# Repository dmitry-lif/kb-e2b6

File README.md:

# KB-E2B6: your own illuminated controls, as a USB keyboard

> [!NOTE]
> **This project is still a work in progress.** Some materials are missing (photos, measurements, a few sections of the docs). Everything still open is marked:
>
> -  a missing piece, with a note in italics on what will go there;
> - the **WORK IN PROGRESS** bar at the top of a page: that page still has open items.

KB-E2B6 is a small (45 × 35 mm) open-source controller for physical controls. You connect up to two rotary encoders with push switches and six push buttons, all of them backlit if you like, and run one USB cable to the host. The host sees an ordinary USB keyboard. You choose once, in a web page (the configurator), what each control sends, and the controller remembers this setup.

You can bring your own encoders and buttons, or start from the **[REFERENCE KIT](docs/kit.md)**: the controller with the encoders, buttons, adapter boards and cables I use myself, tested together, so you have everything you need to hook it up.

I built it for the Android head unit in my car, but nothing about it is car-specific. It should work with anything that accepts a USB keyboard: a PC or media centre, a phone or tablet, a Raspberry Pi, a robot, a simulator panel, or any project that needs a few good physical controls.

> Just want to use it? → **[GETTING STARTED](docs/getting-started.md)**.

**How it fits together.** Up to two backlit rotary encoders and six backlit push buttons plug into the 45 × 35 mm controller. One USB cable goes to the host (a car head unit, PC, phone or robot), which sees an ordinary keyboard. You set it up once from a computer with the configurator; on Android, the optional Key Mapper app turns the keys into app actions, such as F1 → open the maps app.

## Why I built it

When the infotainment system of my 2020 KIA Sorento died, I replaced it with a 10" Android head unit: big screen, modern UI, and not a single physical button. Head units with buttons exist, but they usually have only one or a few, the buttons take space away from the screen, and the units cost more. What I really wanted were controls that look like they came with the car: built into the dashboard, backlit like the originals, sized to fit the tight frame around the new unit, and doing exactly what I want.

Android already understands a USB keyboard, so the controls didn't need a custom app or driver. What was missing was a small controller that reads encoders and buttons, drives their backlight, runs from the head unit's USB port and is easy to set up. For the actions a plain key press can't reach, I use the open-source **[KEY MAPPER](https://github.com/keymapperorg/KeyMapper)** app on the head unit.

Key Mapper turned out to matter for a second reason. Once the controller is installed behind the dashboard, getting it back out to plug into a laptop is a real job, however easy the configurator is. So some of my buttons send plain F-keys, and Key Mapper on the head unit decides what they do. When I change my mind about a button, I remap it on the screen in a minute, without touching the dash. → [The full story](docs/story.md)

**The head unit with the KB-E2B6 behind the dashboard.** Day and night, real photos.

## At a glance

- **Inputs:** 2 rotary encoders with push switch and 6 push buttons. Use as many as you need; unused ports do nothing.
- **Backlight:** every control can be lit, softly enough for night driving. All the LEDs share one supply that the controller dims together. The button on the board turns them on or off and steps the brightness, and the level is remembered. Your own controls do this only if you give them backlight actions (I use long presses).
- **Adapter boards:** small boards that connect the reference kit's encoders and buttons (or your own) to the controller with ready-made cables (an encoder sits on its adapter; a button's adapter sits in its cable). Their solder jumpers (pairs of pads you join with solder) set each control's LED current up or down, so different LEDs can be matched in brightness and none gets brighter than you set.
- **Gestures:** short press, long press and repeat-while-held on every push button and encoder push switch; one action per detent in each direction on encoders with as many pulses as detents.
- **Actions:** keyboard and media keys from a curated list: volume, mute, play/pause, next/previous, Home, Back, Menu, screen brightness, arrows, Enter, Esc, F1–F24, letters and digits, with Ctrl/Shift/Alt/Win combinations, plus backlight actions (on/off, brighter, dimmer).
- **Configuration:** a plain web page you open from disk in Google Chrome, Microsoft Edge, Brave or Opera (other Chromium-based browsers should work too) on a Linux (with a udev rule), Windows or Mac computer (Windows and Mac not tested yet). Pick actions from dropdowns, click **Save to device**. No app, driver, account or internet connection.
- **Power:** from the USB port it plugs into: 17 mA for the board alone, about 30 mA with the 8 controls of my [control box](#the-hardware) lit for daylight.

## Car-minded details

The car shaped a few decisions:

- ESD protection diodes on all 12 input lines and on the USB data lines.
- The LED rail goes through a current-limited switch, an "eFuse" (TPS2553, about 135 mA). A shorted LED cable should be current-limited instead of dragging down the USB supply.
- Flash holds two setup slots: the current setup and the previous one. A save goes to the spare slot, which is read back and checked before the board switches to it, so a power cut in the middle of a save should leave the previous setup in place.
- There's no built-in fallback mapping. If the newest saved setup is damaged, the board should fall back to the previous one you saved, if there is one; **if there's no usable setup at all, the controls stay silent**.
- It runs from 5 V USB only. It is **not** for direct connection to a car's 12 V, and it is not certified automotive equipment.

## Get going in 3 steps

1. **Connect the controls.** Encoders go to `ENC 1` / `ENC 2`, buttons to `BTN 1` … `BTN 6` (names on the back of the board; the top shows E1, E2, B1–B6). The reference encoders and buttons sit on small adapter boards with ready-made cables, and the plugs only fit one way: plug each cable so its red wire is on `LED+` at both ends ([why](docs/wiring.md#cables-to-the-adapter-boards)). You can also wire up your own controls. **Using an RGB encoder? Solder its colour jumper first** (see [the hardware](#the-hardware)).
2. **Configure it once, on a computer.** Download the project ([on GitHub](https://github.com/dmitry-lif/kb-e2b6): green *Code* button → *Download ZIP*), unzip it, open `web_config/index.html` in Chrome, Edge, Brave or Opera, plug the board in, click **Connect device**, choose what each control does and click **Save to device**. **A new board does nothing until you've done this.** Use a USB cable that carries data. (Firefox, Safari and phone or head-unit browsers can't do this step.) **On Linux, once, before you connect**, run this in a terminal from the unzipped folder:

   ```bash
   web_config/linux/install-udev-rule.sh
   ```

   Still can't connect on Linux: [this check](docs/troubleshooting.md#linux-still-cant-connect).

3. **Plug it into your head unit, PC or tablet.** The red status LED should show its heartbeat (two short flashes every second) and your controls should work. Fast blinking means there's no saved setup: back to [step 2](#get-going-in-3-steps).

> Step by step, with what you should see at each point: **[GETTING STARTED](docs/getting-started.md)**.

**The configurator.** The web page connected to a board: the toolbar with **Save to device**, the status strip (serial number, firmware version, *Config A* / *Config B*) and cards for the general settings, the encoders and the buttons, each set with dropdowns. The labels match the real page; the layout in this picture is approximate.

## The hardware

The controller works with any encoders and buttons that switch to ground. The adapter boards make the reference parts plug-and-play and set their LED current with solder jumpers. Everything is in [`hardware/`](hardware/): KiCad 9 projects plus Gerber, BOM and pick-and-place files for JLCPCB in each `manufacturing/` folder (Gerbers only for the cover plate).

| Board | What it is | KiCad project |
|---|---|---|
| **KB-E2B6 controller** | 45 × 35 mm, STM32G474, USB-C, 2 × 6-pin encoder ports, 6 × 4-pin button ports, on-board button (LED on/off and brightness), status LED, 4-pin SWD header | [`hardware/kb_e2b6_hw_v2.kicad_pro`](hardware/kb_e2b6_hw_v2.kicad_pro) |
| **Encoder adapter** | Holds an EC12 encoder with a single-colour LED; jumpers set the LED current | [`hardware/encoder_db/`](hardware/encoder_db/) |
| **RGB encoder adapter** | Holds an EC12 RGB encoder; jumpers set the LED current and the colour. **No colour is selected from the factory** (see below) | [`hardware/encoder_rgb_db/`](hardware/encoder_rgb_db/) |
| **Button adapter** | Sits in the cable between the controller and an LED push button; jumpers set the LED current | [`hardware/button_db/`](hardware/button_db/) |
| **Cover plate** | 45 × 35 mm PCB lid for the controller | [`hardware/cover/`](hardware/cover/) |

> [!IMPORTANT]
> **RGB encoder adapter: choose the colour before you install it.** Its three colour jumpers (R, G, B) all come open, so the encoder's LED stays dark until you bridge one of them with a soldering iron. Bridge one only: colours can't be mixed. Which jumper is which: [Hardware notes](docs/hardware.md#rgb-encoder-adapter).

> [!NOTE]
> One detail worth a look is the RGB encoder adapter. The RGB encoders I use as reference parts share one pin between the switch and the LEDs, so the usual dimming (switching the LED's minus side) can't work. A small P-MOSFET on the adapter, driven by the controller's dimmed LED pair, switches the LED supply instead: same cable, same port, no firmware change.

> How the boards work, part by part, with the trade-offs: **[Hardware notes](docs/hardware.md)**. Making your own: **[Building your own](docs/building.md)**.

**The controller, rev 2.1.** KiCad 3D render of the 45 × 35 mm board: the 6-pin encoder ports (E1, E2) and 4-pin button ports (B1–B6) along the two long edges, the STM32 in the middle, the USB-C socket on the left edge, and the status LED, the on-board button and the SWD connection (3V3, SWIO, SWCLK, GND) on the right.

**The real controller, all eight ports cabled.** Left: with the cover plate screwed on. Right: the back, where the silkscreen names every port (`ENC 1`, `ENC 2`, `BTN 1` … `BTN 6`) and its pins.

**The controller with its controls.** Two encoders sit on their adapter boards; each of the six push buttons connects through a button adapter in its cable. Every control has one cable to its port.

**A control box built around the controller.** Left: the front panel, with two backlit encoders and six backlit buttons in different colours, at a brightness clearly visible in daylight: the whole box draws about 30 mA ([Specs](#specs)). Right: the box opened, with the controller at the bottom, the encoders and buttons with their adapter boards in the lid, and the cables between them. One example of what you can build; the box and these controls are not part of the [reference kit](docs/kit.md).

## Firmware and configurator

The firmware is Rust on [Embassy](https://embassy.dev): `no_std`, no heap, and an input scan loop that never waits on anything. Its settings are a fixed-size, CRC-checked binary validated by the same Rust code in the firmware and in the `crs-pack` command-line tool. A setup only takes effect at boot, so **Save to device** writes the spare setup slot and restarts the board (a couple of seconds). That keeps a single, well-trodden startup path instead of a second "apply live" path.

The configurator is plain HTML and JavaScript with no build step. It talks to the board over WebHID (the USB access built into Chromium-based browsers) through a separate vendor-defined HID interface, next to the keyboard.

- Build, flash, recovery: [`firmware/README.md`](firmware/README.md)
- How the firmware is organised, and why: [`firmware/docs/ARCHITECTURE.md`](firmware/docs/ARCHITECTURE.md)
- Using the configurator, with screenshots and example setups: [`docs/configuring.md`](docs/configuring.md); its files: [`web_config/README.md`](web_config/README.md)

## Status

This is the first public snapshot: controller rev 2.1, adapter boards rev 2.0, firmware 2.1.0.

## Specs

| | |
|---|---|
| Inputs | 2 rotary encoders (with push switch), 6 push buttons, 1 on-board button (LED on/off and brightness) |
| Output to host | USB HID keyboard + consumer (media) keys; also a serial debug console (CDC) and a WebHID configuration interface |
| Host connector | USB-C (USB 2.0 full speed) |
| Control connectors | JST GH-compatible 1.25 mm: 2 × 6-pin (encoders), 6 × 4-pin (buttons) |
| Programming | 4-pin 2.54 mm SWD header (no reset pin) |
| Power | 5 V from USB only. **Not** for direct connection to a car's 12 V |
| LEDs | One shared 5 V rail, current-limited (TPS2553, ~135 mA nominal), PWM-dimmed together at 1 kHz |
| Consumption | 17 mA for the board alone. With 8 controls lit (2 encoders, 6 buttons): about 19 mA at the lowest brightness, about 30 mA at a brightness clearly visible in daylight, as in the [control box photo](#the-hardware). Measured on that box; other LEDs not tested |
| MCU | STM32G474CBT6, 170 MHz, 128 KiB flash, no crystal |
| Size | 45 × 35 mm, 4 × M2 mounting holes |
| Configure with | Google Chrome, Microsoft Edge, Brave or Opera (Chromium-based browsers) on a Linux (needs a udev rule), Windows or Mac computer (Windows and Mac not tested yet); the page runs locally |

## FAQ

**Does it work with my head unit?** If it accepts a USB keyboard, it should. Easy test before you buy: plug any USB keyboard with media keys into the head unit's USB port. If the volume and arrow keys work, the controller should work too. In my own car: a **10" Mekede DUDU 4 running Android 10**. Mapping some Android system actions with Key Mapper has limits: I was surprised to find that many trivial ones need extra permissions (easy to grant by following Key Mapper's in-app guides), and some even need further Android tweaks over the debug interface. I didn't go that far: for my use case the standard keys were enough.

**Does the backlight follow my car's dash dimmer?** No, the controller has no input for it. You set the level yourself and it stays there. You can also give your controls backlight actions (I put them on long presses, as a secondary function).

**Can I configure it on the head unit itself?** No. Browsers on Android (and Firefox and Safari anywhere) can't talk to USB devices this way. Use a computer once; the setup stays in the controller.

**Can I change what a button does after it's installed?** Yes: reconnect it to a computer and save a new setup, or give the controls arbitrary keys (say F-keys) once and remap them on the host, on Android with [Key Mapper](https://github.com/keymapperorg/KeyMapper), on a PC with any key-remapping tool. Backlight actions can only be assigned in the configurator. Details: [Getting started](docs/getting-started.md#4-plug-it-into-your-host).

**What if I mess up the setup?** By design, the board checks every setup before saving it, refuses an invalid one and keeps the old setup. Just fix it in the configurator and click **Save to device** again.

**Can I use my own encoders and buttons?** Yes. Encoders: any EC11/EC12-style one with as many pulses as detents. Buttons: any momentary type. Both must switch to ground. LEDs need their own series resistor (the adapter boards have them). What I learned picking mine: [choosing controls](docs/choosing-controls.md).

**Can I update the firmware over USB?** Not in 2.1.0. Firmware updates need an SWD probe; the configurator only changes the setup.

## Get one, build one, or get in touch

- **The reference kit:** the controller with tested encoders, buttons, adapter boards and cables. What's in it, what you supply and what you still do yourself: **[THE REFERENCE KIT](docs/kit.md)**.
- **Build your own:** order the boards from the files in `hardware/manufacturing/` and `hardware/*/manufacturing/` and flash the MCU ([Building your own](docs/building.md)), then prepare the controls ([Preparing and wiring the controls](docs/wiring.md)) and configure it ([Getting started](docs/getting-started.md)).
- **Feedback, bugs, ideas:** [open an issue](https://github.com/dmitry-lif/kb-e2b6/issues). It's a one-person hobby project, so replies may take a while, but I'd like to hear how you use it.

## Documentation

| | |
|---|---|
| [The reference kit](docs/kit.md) | What's in the kit, what you supply, what you still do |
| [Getting started](docs/getting-started.md) | Connecting the controls, configuring, the backlight, plugging into the host |
| [Troubleshooting, limitations and safety](docs/troubleshooting.md) | Symptoms, configurator messages, known limits, test status, safety |
| [Hardware notes](docs/hardware.md) | How the controller and the adapter boards work, and why |
| [Building your own](docs/building.md) | Ordering the boards, the SWD header, flashing the firmware, first checks |
| [Preparing and wiring the controls](docs/wiring.md) | Ports, wiring rules, soldering the controls onto the adapter boards, cables, bench checks: for the kit's controls and your own |
| [Configuring the controller](docs/configuring.md) | Quick start with screenshots, every option of the configurator, example setups |
| [Firmware](firmware/README.md) | Build, flash, architecture, specs, recovery |
| [The story](docs/story.md) · [Choosing controls](docs/choosing-controls.md) · [Car integration](docs/car-integration.md) | Background, parts I tried, putting it into a car |

## License

© 2026 Dmitry Lifshits. Code (firmware, tools, configurator): [MIT](LICENSE-MIT) or [Apache-2.0](LICENSE-APACHE). Hardware: [CERN-OHL-S-2.0](hardware/LICENSE): if you make and distribute boards based on a modified design, you share the modified design files under the same licence. Docs and images: [CC BY 4.0](docs/LICENSE.md), except a few third-party product images listed there. Third-party crates: [THIRD_PARTY_LICENSES.md](THIRD_PARTY_LICENSES.md).

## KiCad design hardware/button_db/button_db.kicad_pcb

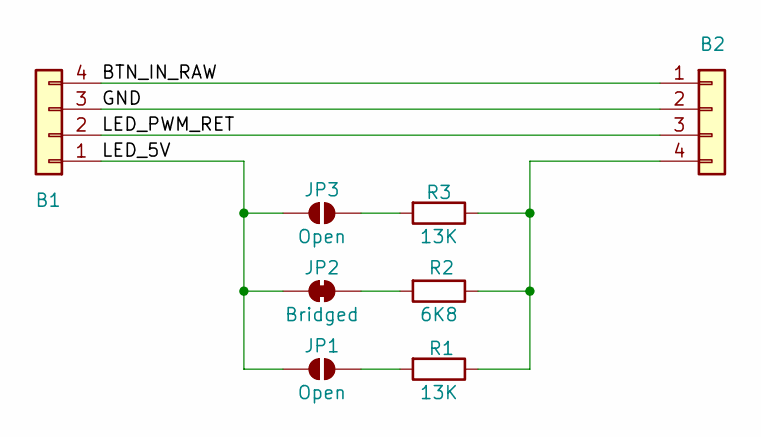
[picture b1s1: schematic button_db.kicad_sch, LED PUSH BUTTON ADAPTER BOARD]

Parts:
B1, B2: Conn_01x04; JST_GH_SM04B-GHS-TB_1x04-1MP_P1.25mm_Horizontal; JLCPCB Part # C51940118
JP1, JP3: Open; SolderJumper-2_P1.3mm_Open_RoundedPad1.0x1.5mm
JP2: Bridged; SolderJumper-2_P1.3mm_Bridged_RoundedPad1.0x1.5mm
R1, R3: 13K; R_0603_1608Metric; JLCPCB Part # C22797
R2: 6K8; R_0603_1608Metric; JLCPCB Part # C23212

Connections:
/BTN_IN_RAW: B1.4, B2.1
/GND: B1.3, B2.2
/LED_5V: B1.1, JP1.2 (B), JP2.2 (B), JP3.2 (B)
/LED_PWM_RET: B1.2, B2.3
unnamed: B2.4, R1.1, R2.1, R3.1
unnamed: JP1.1 (A), R1.2
unnamed: JP2.1 (A), R2.2
unnamed: JP3.1 (A), R3.2

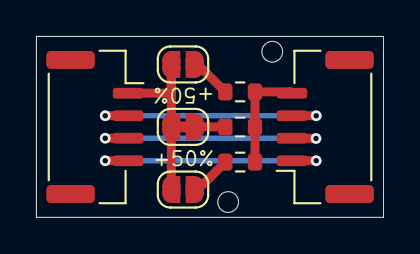
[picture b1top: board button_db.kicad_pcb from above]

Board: 2 copper layers, 19.3 x 10.0 mm, 10 parts (2 on the bottom side), 8 nets.

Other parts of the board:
TH1, TH2: JLCPCB_ToolingHole_1.152mm

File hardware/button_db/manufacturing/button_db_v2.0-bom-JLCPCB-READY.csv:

Comment,Designator,Footprint,JLCPCB Part #
Conn_01x04,"B1,B2",Connector_JST:JST_GH_SM04B-GHS-TB_1x04-1MP_P1.25mm_Horizontal,C51940118
13K,"R1,R3",Resistor_SMD:R_0603_1608Metric,C22797
6K8,R2,Resistor_SMD:R_0603_1608Metric,C23212

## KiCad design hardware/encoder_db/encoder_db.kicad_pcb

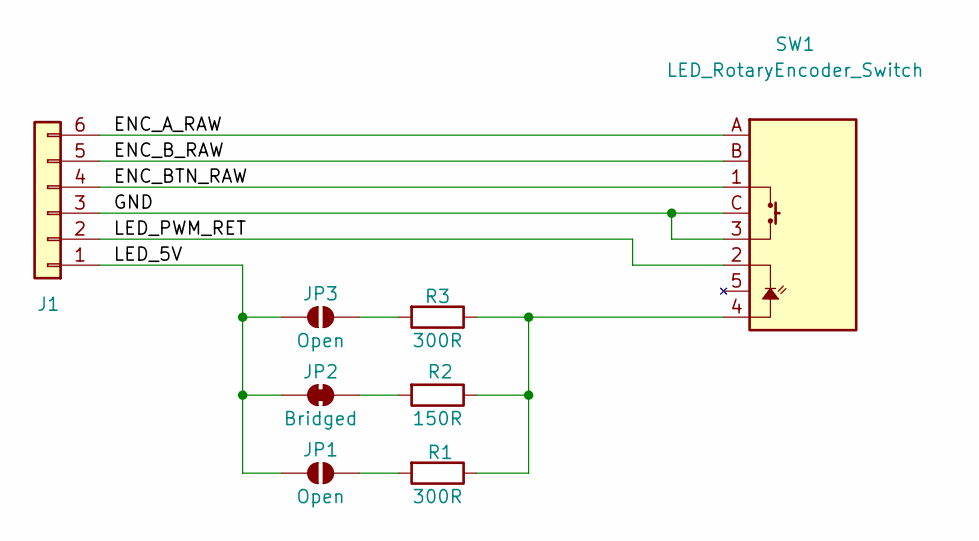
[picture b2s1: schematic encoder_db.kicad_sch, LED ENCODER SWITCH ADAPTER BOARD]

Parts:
J1: Conn_01x06; JST_GH_SM06B-GHS-TB_1x06-1MP_P1.25mm_Horizontal; JLCPCB Part # C51940119
JP1, JP3: Open; SolderJumper-2_P1.3mm_Open_RoundedPad1.0x1.5mm
JP2: Bridged; SolderJumper-2_P1.3mm_Bridged_RoundedPad1.0x1.5mm
R1, R3: 300R; R_0603_1608Metric; JLCPCB Part # C23025
R2: 150R; R_0603_1608Metric; JLCPCB Part # C22808
SW1: LED_RotaryEncoder_Switch; RotaryEncoder_EC12_LED_Switch_Vertical

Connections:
/ENC_A_RAW: J1.6, SW1.A
/ENC_BTN_RAW: J1.4, SW1.1 (SW2)
/ENC_B_RAW: J1.5, SW1.B
/GND: J1.3, SW1.3 (SW1), SW1.C
/LED_5V: J1.1, JP1.2 (B), JP2.2 (B), JP3.2 (B)
/LED_PWM_RET: J1.2, SW1.2 (LED-)
unnamed: JP1.1 (A), R1.2
unnamed: JP2.1 (A), R2.2
unnamed: JP3.1 (A), R3.2
unnamed: R1.1, R2.1, R3.1, SW1.4 (LED+)

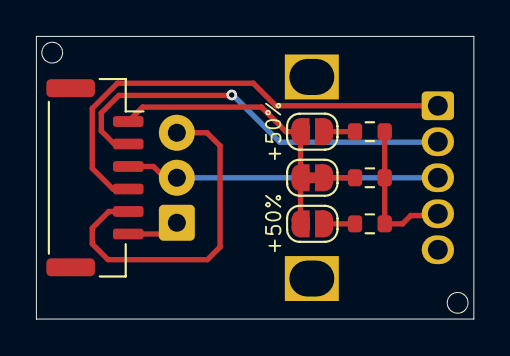
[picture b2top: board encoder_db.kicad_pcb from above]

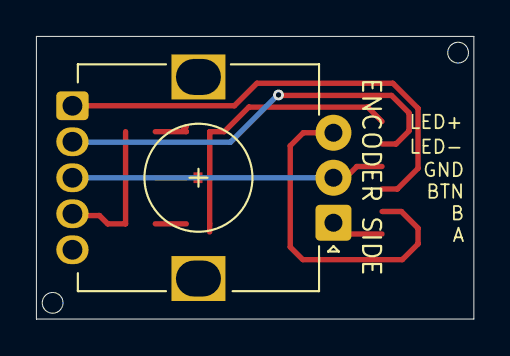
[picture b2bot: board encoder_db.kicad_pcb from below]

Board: 2 copper layers, 24.3 x 15.7 mm, 10 parts (3 on the bottom side), 10 nets.

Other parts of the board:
TH1, TH2: JLCPCB_ToolingHole_1.152mm

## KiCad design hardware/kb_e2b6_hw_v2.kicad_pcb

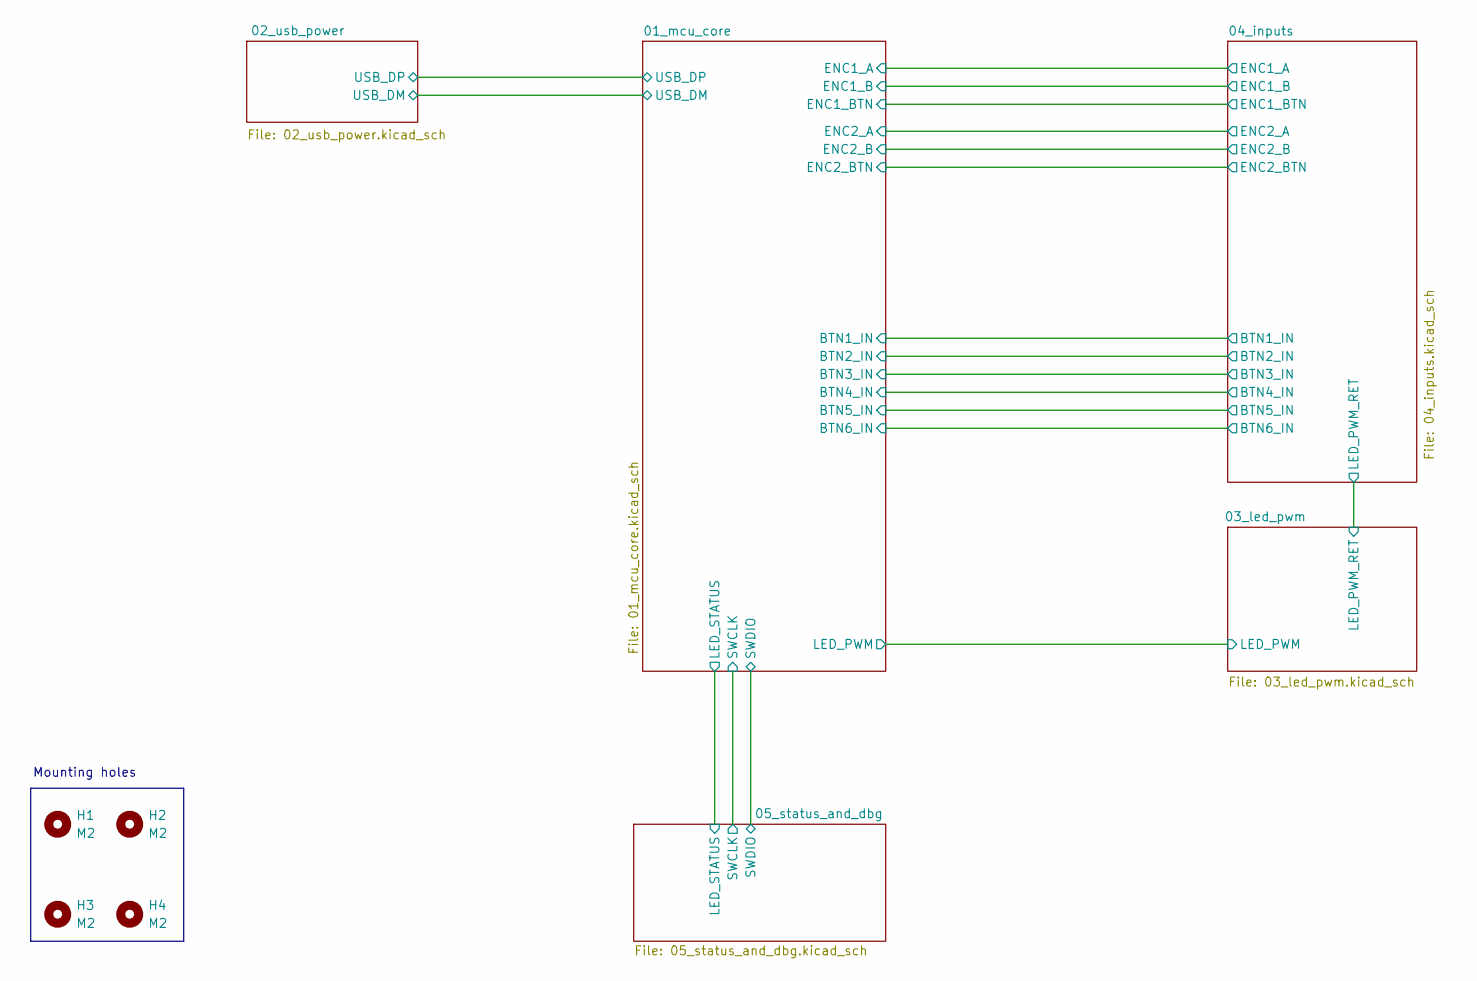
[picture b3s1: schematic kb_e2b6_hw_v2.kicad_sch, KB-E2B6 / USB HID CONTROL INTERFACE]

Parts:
H1, H2, H3, H4: M2; MountingHole_2.2mm_M2

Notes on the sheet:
Mounting holes

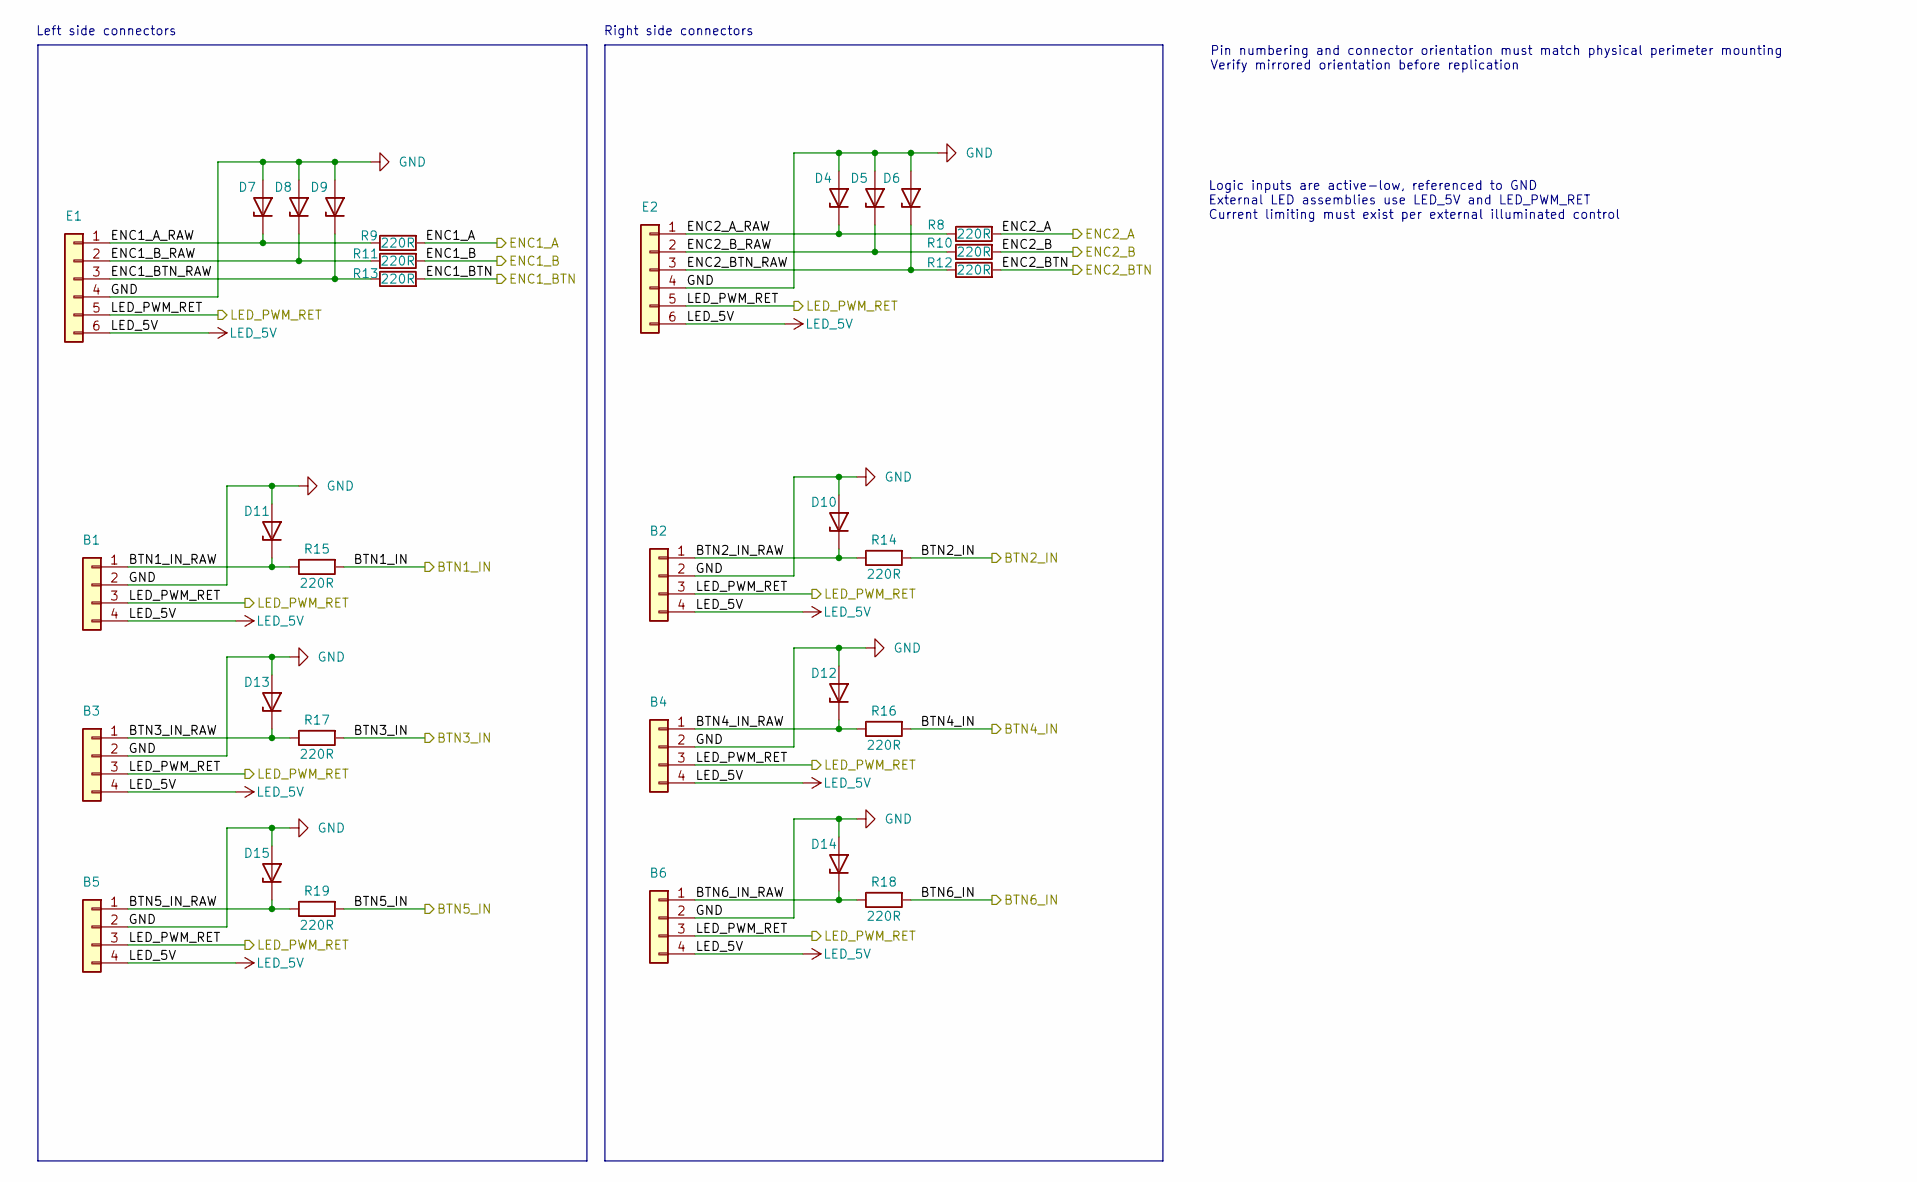
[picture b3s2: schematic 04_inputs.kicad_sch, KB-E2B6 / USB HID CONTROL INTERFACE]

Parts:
B1, B2, B3, B4, B5, B6: Conn_01x04; JST_GH_SM04B-GHS-TB_1x04-1MP_P1.25mm_Horizontal; JLCPCB Part # C51940118
D4, D5, D6, D7, D8, D9, D10, D11, D12, D13, D14, D15: H3V3U10B; D_SOD-882; JLCPCB Part # C20615782
E1, E2: Conn_01x06; JST_GH_SM06B-GHS-TB_1x06-1MP_P1.25mm_Horizontal; JLCPCB Part # C51940119
R8, R9, R10, R11, R12, R13, R14, R15, R16, R17, R18, R19: 220R; R_0402_1005Metric; JLCPCB Part # C25091

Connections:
/01_mcu_core/BTN1_IN: R15.2; also elsewhere on the board
/01_mcu_core/BTN2_IN: R14.2; also elsewhere on the board
/01_mcu_core/BTN3_IN: R17.2; also elsewhere on the board
/01_mcu_core/BTN4_IN: R16.2; also elsewhere on the board
/01_mcu_core/BTN5_IN: R19.2; also elsewhere on the board
/01_mcu_core/BTN6_IN: R18.2; also elsewhere on the board
/01_mcu_core/ENC1_A: R9.2; also elsewhere on the board
/01_mcu_core/ENC1_B: R11.2; also elsewhere on the board
/01_mcu_core/ENC1_BTN: R13.2; also elsewhere on the board
/01_mcu_core/ENC2_A: R8.2; also elsewhere on the board
/01_mcu_core/ENC2_B: R10.2; also elsewhere on the board
/01_mcu_core/ENC2_BTN: R12.2; also elsewhere on the board
/03_led_pwm/LED_PWM_RET: B1.3, B2.3, B3.3, B4.3, B5.3, B6.3, E1.5, E2.5; also elsewhere on the board
/04_inputs/BTN1_IN_RAW: B1.1, D11.1 (K), R15.1
/04_inputs/BTN2_IN_RAW: B2.1, D10.1 (K), R14.1
/04_inputs/BTN3_IN_RAW: B3.1, D13.1 (K), R17.1
/04_inputs/BTN4_IN_RAW: B4.1, D12.1 (K), R16.1
/04_inputs/BTN5_IN_RAW: B5.1, D15.1 (K), R19.1
/04_inputs/BTN6_IN_RAW: B6.1, D14.1 (K), R18.1
/04_inputs/ENC1_A_RAW: D7.1 (K), E1.1, R9.1
/04_inputs/ENC1_BTN_RAW: D9.1 (K), E1.3, R13.1
/04_inputs/ENC1_B_RAW: D8.1 (K), E1.2, R11.1
/04_inputs/ENC2_A_RAW: D4.1 (K), E2.1, R8.1
/04_inputs/ENC2_BTN_RAW: D6.1 (K), E2.3, R12.1
/04_inputs/ENC2_B_RAW: D5.1 (K), E2.2, R10.1
GND: B1.2, B2.2, B3.2, B4.2, B5.2, B6.2, D4.2 (A), D5.2 (A), D6.2 (A), D7.2 (A), D8.2 (A), D9.2 (A), D10.2 (A), D11.2 (A), D12.2 (A), D13.2 (A), D14.2 (A), D15.2 (A), E1.4, E2.4; also elsewhere on the board
LED_5V: B1.4, B2.4, B3.4, B4.4, B5.4, B6.4, E1.6, E2.6; also elsewhere on the board

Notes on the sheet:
Right side connectors
Pin numbering and connector orientation must match physical perimeter mounting Verify mirrored orientation before replication
Left side connectors
Logic inputs are active-low, referenced to GND External LED assemblies use LED_5V and LED_PWM_RET Current limiting must exist per external illuminated control

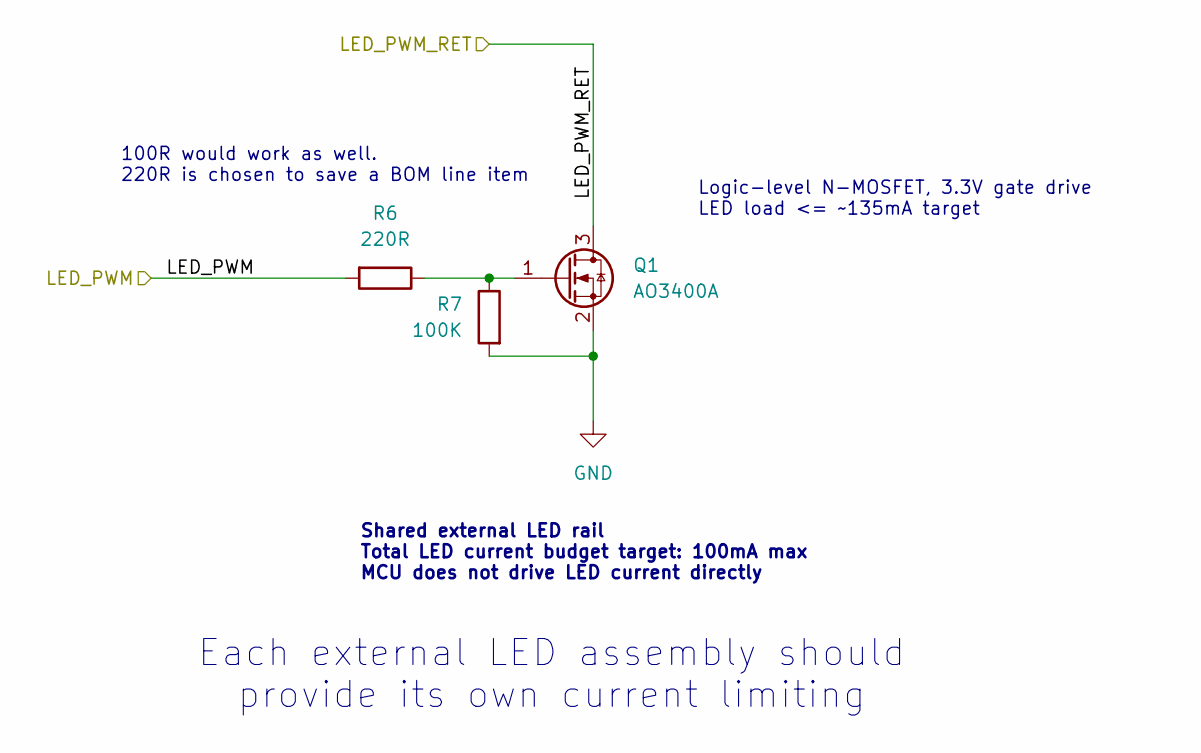
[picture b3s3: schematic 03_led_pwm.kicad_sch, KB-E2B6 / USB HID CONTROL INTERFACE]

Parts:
Q1: AO3400A; SOT-23; JLCPCB Part # C20917
R6: 220R; R_0402_1005Metric; JLCPCB Part # C25091
R7: 100K; R_0402_1005Metric; JLCPCB Part # C25741

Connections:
/01_mcu_core/LED_PWM: R6.2; also elsewhere on the board
/03_led_pwm/LED_PWM_RET: Q1.3 (D); also elsewhere on the board
GND: Q1.2 (S), R7.2; also elsewhere on the board
unnamed: Q1.1 (G), R6.1, R7.1

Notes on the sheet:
Shared external LED rail Total LED current budget target: 100mA max MCU does not drive LED current directly
Logic-level N-MOSFET, 3.3V gate drive LED load <= ~135mA target
100R would work as well. 220R is chosen to save a BOM line item
Each external LED assembly should provide its own current limiting

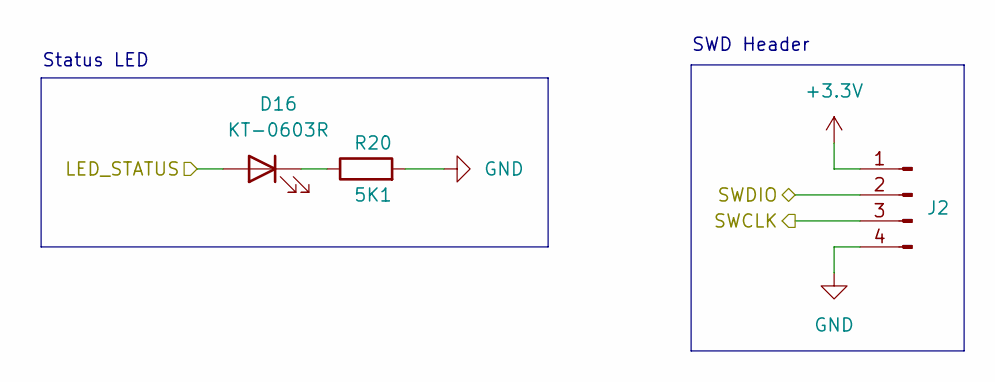
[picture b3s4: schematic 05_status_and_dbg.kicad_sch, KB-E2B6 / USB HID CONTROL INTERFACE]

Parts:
D16: KT-0603R; LED_0603_1608Metric; JLCPCB Part # C2286
J2: Conn_01x04_Pin; PinHeader_1x04_P2.54mm_Vertical
R20: 5K1; R_0402_1005Metric; JLCPCB Part # C25905

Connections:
+3.3V: J2.1; also elsewhere on the board
/01_mcu_core/LED_STATUS: D16.2 (A); also elsewhere on the board
/01_mcu_core/SWCLK: J2.3; also elsewhere on the board
/01_mcu_core/SWDIO: J2.2; also elsewhere on the board
GND: J2.4, R20.2; also elsewhere on the board
unnamed: D16.1 (K), R20.1

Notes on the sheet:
Status LED
SWD Header

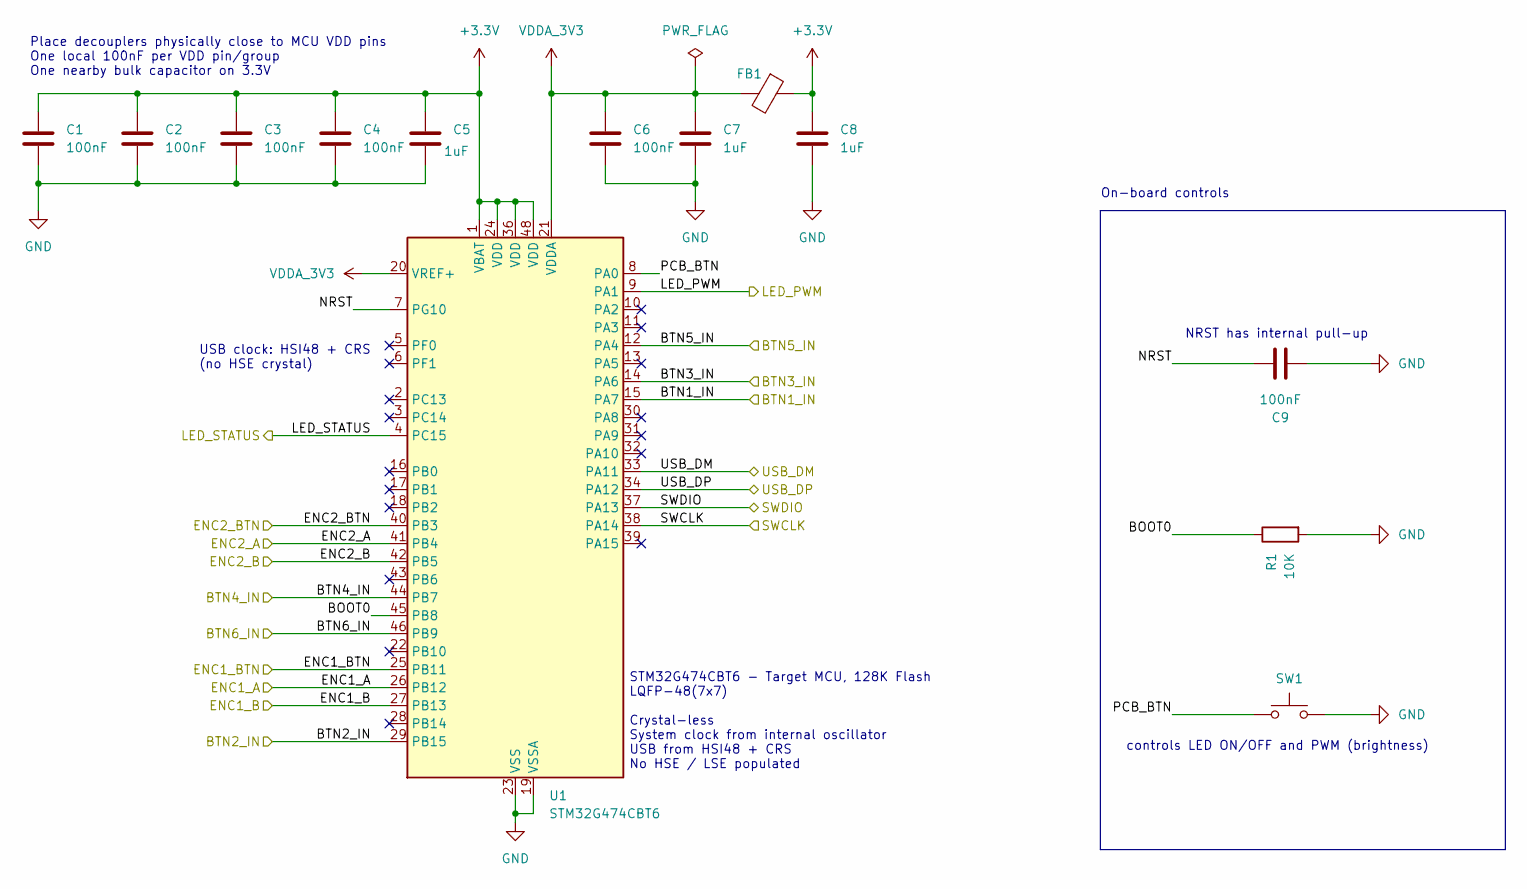
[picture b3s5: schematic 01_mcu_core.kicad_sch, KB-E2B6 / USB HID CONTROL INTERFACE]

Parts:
C1, C2, C3, C4, C6, C9: 100nF; C_0402_1005Metric; JLCPCB Part # C1525
C5, C7, C8: 1uF; C_0402_1005Metric; JLCPCB Part # C52923
FB1: BLM18PG121SN1D; L_0603_1608Metric; JLCPCB Part # C14709
R1: 10K; R_0402_1005Metric; JLCPCB Part # C25744
SW1: TS-1088-AR02016; SW_SPST_TS-1088-xR020; JLCPCB Part # C720477
U1: STM32G474CBT6; LQFP-48_7x7mm_P0.5mm; JLCPCB Part # C5270356

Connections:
+3.3V: C1.1, C2.1, C3.1, C4.1, C5.1, C8.1, FB1.1, U1.1 (VBAT), U1.24 (VDD), U1.36 (VDD), U1.48 (VDD); also elsewhere on the board
/01_mcu_core/BOOT0: R1.1, U1.45 (PB8)
/01_mcu_core/BTN1_IN: U1.15 (PA7); also elsewhere on the board
/01_mcu_core/BTN2_IN: U1.29 (PB15); also elsewhere on the board
/01_mcu_core/BTN3_IN: U1.14 (PA6); also elsewhere on the board
/01_mcu_core/BTN4_IN: U1.44 (PB7); also elsewhere on the board
/01_mcu_core/BTN5_IN: U1.12 (PA4); also elsewhere on the board
/01_mcu_core/BTN6_IN: U1.46 (PB9); also elsewhere on the board
/01_mcu_core/ENC1_A: U1.26 (PB12); also elsewhere on the board
/01_mcu_core/ENC1_B: U1.27 (PB13); also elsewhere on the board
/01_mcu_core/ENC1_BTN: U1.25 (PB11); also elsewhere on the board
/01_mcu_core/ENC2_A: U1.41 (PB4); also elsewhere on the board
/01_mcu_core/ENC2_B: U1.42 (PB5); also elsewhere on the board
/01_mcu_core/ENC2_BTN: U1.40 (PB3); also elsewhere on the board
/01_mcu_core/LED_PWM: U1.9 (PA1); also elsewhere on the board
/01_mcu_core/LED_STATUS: U1.4 (PC15); also elsewhere on the board
/01_mcu_core/NRST: C9.2, U1.7 (PG10)
/01_mcu_core/PCB_BTN: SW1.1, U1.8 (PA0)
/01_mcu_core/SWCLK: U1.38 (PA14); also elsewhere on the board
/01_mcu_core/SWDIO: U1.37 (PA13); also elsewhere on the board
/01_mcu_core/USB_DM: U1.33 (PA11); also elsewhere on the board
/01_mcu_core/USB_DP: U1.34 (PA12); also elsewhere on the board
GND: C1.2, C2.2, C3.2, C4.2, C5.2, C6.2, C7.2, C8.2, C9.1, R1.2, SW1.2, U1.19 (VSSA), U1.23 (VSS), U1.35 (VSS), U1.47 (VSS); also elsewhere on the board
VDDA_3V3: C6.1, C7.1, FB1.2, U1.20 (VREF+), U1.21 (VDDA)

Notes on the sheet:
controls LED ON/OFF and PWM (brightness)
NRST has internal pull-up
Place decouplers physically close to MCU VDD pins One local 100nF per VDD pin/group One nearby bulk capacitor on 3.3V
USB clock: HSI48 + CRS (no HSE crystal)
STM32G474CBT6 - Target MCU, 128K Flash LQFP-48(7x7) Crystal-less System clock from internal oscillator USB from HSI48 + CRS No HSE / LSE populated
On-board controls

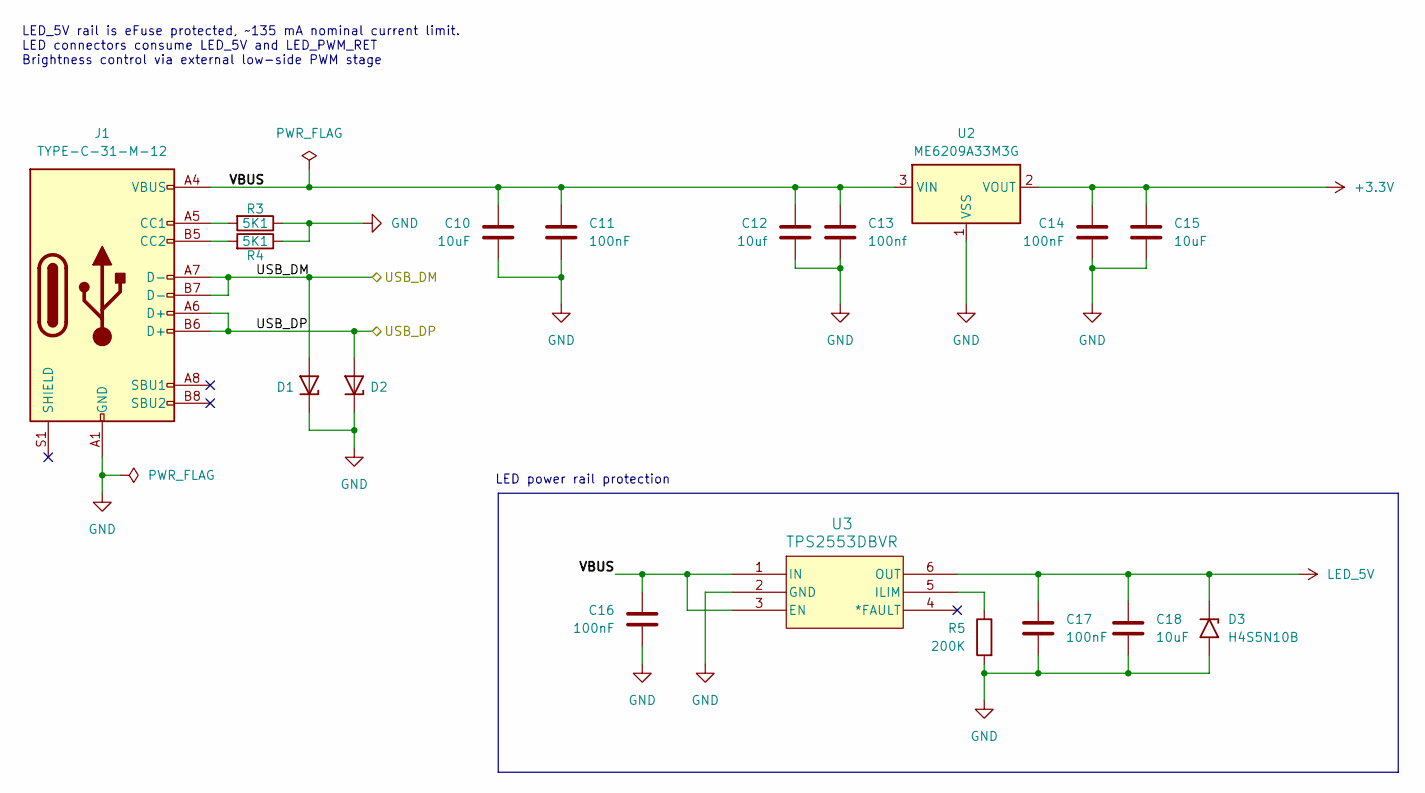
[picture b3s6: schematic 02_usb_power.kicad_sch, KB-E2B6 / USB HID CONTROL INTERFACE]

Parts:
C10, C15, C18: 10uF; C_0603_1608Metric; JLCPCB Part # C96446
C11, C14, C16, C17: 100nF; C_0402_1005Metric; JLCPCB Part # C1525
C12: 10uf; C_0603_1608Metric; JLCPCB Part # C96446
C13: 100nf; C_0402_1005Metric; JLCPCB Part # C1525
D1, D2: H5VU10BB; D_SOD-882; JLCPCB Part # C20615786
D3: H4S5N10B; D_SOD-882; JLCPCB Part # C20617910
J1: TYPE-C-31-M-12; USB_C_Receptacle_HRO_TYPE-C-31-M-12; JLCPCB Part # C165948
R3, R4: 5K1; R_0402_1005Metric; JLCPCB Part # C25905
R5: 200K; R_0402_1005Metric; JLCPCB Part # C25764
U2: ME6209A33M3G; SOT-23-3; JLCPCB Part # C83508
U3: TPS2553DBVR; SOT-23-6; JLCPCB Part # C55266

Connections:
+3.3V: C14.1, C15.1, U2.2 (VOUT); also elsewhere on the board
/01_mcu_core/USB_DM: D1.2 (A), J1.A7 (D-), J1.B7 (D-); also elsewhere on the board
/01_mcu_core/USB_DP: D2.2 (A), J1.A6 (D+), J1.B6 (D+); also elsewhere on the board
/02_usb_power/VBUS: C10.1, C11.1, C12.1, C13.1, C16.1, J1.A4 (VBUS), J1.A9 (VBUS), J1.B4 (VBUS), J1.B9 (VBUS), U2.3 (VIN), U3.1 (IN), U3.3 (EN)
GND: C10.2, C11.2, C12.2, C13.2, C14.2, C15.2, C16.2, C17.2, C18.2, D1.1 (K), D2.1 (K), D3.2 (A2), J1.A1 (GND), J1.A12 (GND), J1.B1 (GND), J1.B12 (GND), R3.1, R4.1, R5.2, U2.1 (VSS), U3.2 (GND); also elsewhere on the board
LED_5V: C17.1, C18.1, D3.1 (A1), U3.6 (OUT); also elsewhere on the board
unnamed: J1.A5 (CC1), R3.2
unnamed: J1.B5 (CC2), R4.2
unnamed: R5.1, U3.5 (ILIM)

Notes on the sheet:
LED_5V rail is eFuse protected, ~135 mA nominal current limit. LED connectors consume LED_5V and LED_PWM_RET Brightness control via external low-side PWM stage
LED power rail protection

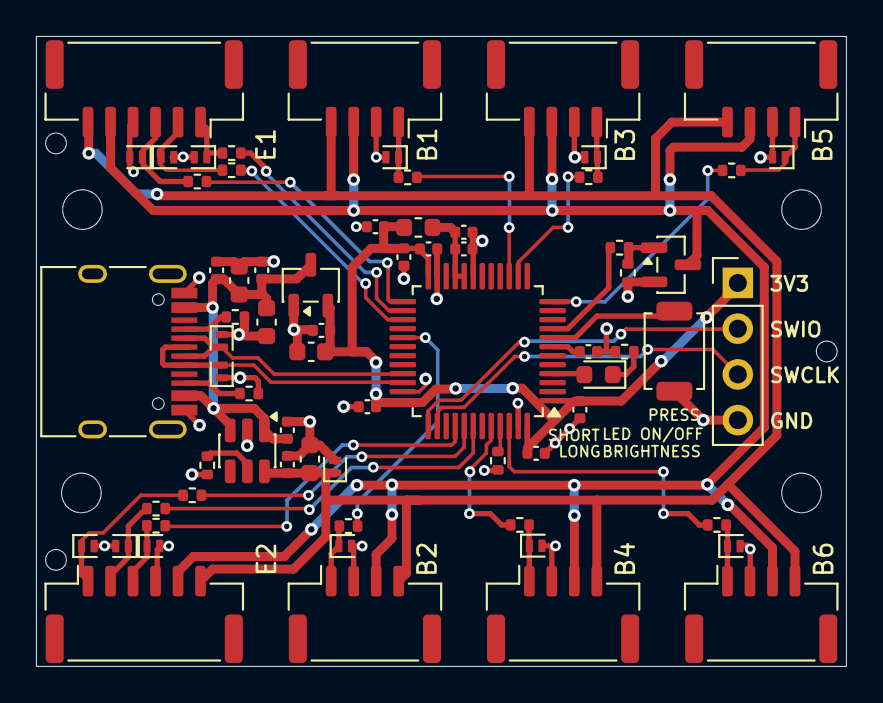
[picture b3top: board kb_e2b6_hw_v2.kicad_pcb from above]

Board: 2 copper layers, 45.0 x 35.0 mm, 76 parts (0 on the bottom side), 44 nets.

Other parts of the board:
TH1: JLCPCB_ToolingHole_1.152mm
TH2, TH3: (no value)

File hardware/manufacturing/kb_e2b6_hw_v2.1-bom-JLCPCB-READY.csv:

Comment,Designator,Footprint,JLCPCB Part #
Conn_01x04,"B1,B2,B3,B4,B5,B6",Connector_JST:JST_GH_SM04B-GHS-TB_1x04-1MP_P1.25mm_Horizontal,C51940118
100nF,"C1,C2,C3,C4,C6,C9,C11,C13,C14,C16,C17",Capacitor_SMD:C_0402_1005Metric,C1525
1uF,"C5,C7,C8",Capacitor_SMD:C_0402_1005Metric,C52923
10uF,"C10,C12,C15,C18",Capacitor_SMD:C_0603_1608Metric,C96446
H5VU10BB,"D1,D2",Diode_SMD:D_SOD-882,C20615786
H4S5N10B,D3,Diode_SMD:D_SOD-882,C20617910
H3V3U10B,"D4,D5,D6,D7,D8,D9,D10,D11,D12,D13,D14,D15",Diode_SMD:D_SOD-882,C20615782
KT-0603R,D16,LED_SMD:LED_0603_1608Metric,C2286
Conn_01x06,"E1,E2",Connector_JST:JST_GH_SM06B-GHS-TB_1x06-1MP_P1.25mm_Horizontal,C51940119
BLM18PG121SN1D,FB1,Inductor_SMD:L_0603_1608Metric,C14709
TYPE-C-31-M-12,J1,Connector_USB:USB_C_Receptacle_HRO_TYPE-C-31-M-12,C165948
AO3400A,Q1,Package_TO_SOT_SMD:SOT-23,C20917
10K,R1,Resistor_SMD:R_0402_1005Metric,C25744
200K,R5,Resistor_SMD:R_0402_1005Metric,C25764
5K1,"R3,R4,R20",Resistor_SMD:R_0402_1005Metric,C25905
220R,"R6,R8,R9,R10,R11,R12,R13,R14,R15,R16,R17,R18,R19",Resistor_SMD:R_0402_1005Metric,C25091
100K,R7,Resistor_SMD:R_0402_1005Metric,C25741
TS-1088-AR02016,SW1,Button_Switch_SMD:SW_SPST_TS-1088-xR020,C720477
STM32G474CBT6,U1,Package_QFP:LQFP-48_7x7mm_P0.5mm,C5270356
ME6209A33M3G,U2,Package_TO_SOT_SMD:SOT-23-3,C83508
TPS2553DBVR,U3,Package_TO_SOT_SMD:SOT-23-6,C55266

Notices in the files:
hardware/01_mcu_core.kicad_sch:
Licensed under CERN-OHL-S-2.0
